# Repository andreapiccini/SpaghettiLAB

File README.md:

<p align="center">
  <a href="https://spaghetti-lab.my.canva.site/">Website</a> •
  <a href="https://spaghetti-lab.my.canva.site/join-newsletter">Newsletter</a>
</p>

# SpaghettiLAB Community

From prototype to product.

SpaghettiLAB Community is the open development platform for learning,
experimenting, and building modular embedded and IoT prototypes. It includes
reference hardware, firmware, local software, protocols, integrations, tests,
and examples without artificial feature restrictions.

A prototype is not automatically suitable for production. Professional
deployments also require qualified hardware, secure provisioning, verified
updates, release traceability, lifecycle maintenance, and accountable support.
Those production capabilities are developed and delivered separately so that
organizations can adopt SpaghettiLAB without weakening the open Community
platform.

## Repository structure

- `hardware/` — Core, Backbone, and Module reference designs.
- `firmware/` — Community firmware, SDKs, examples, and verification.
- `software/` — Local Studio, dashboard, Node-RED integration, and packages.
- `contracts/` — Public, language-neutral protocol contracts and golden fixtures.
- `examples/` — End-to-end example systems.
- `docs/` — Documentation licensing and notices.

The Community hardware tree intentionally contains editable KiCad sources, not
generated manufacturing packages. Official production files, factory tooling,
secure provisioning infrastructure, managed cloud services, and commercial
support are maintained separately.

## Hardware projects

- `hardware/core/core.kicad_pro`
- `hardware/backbone/backbone.kicad_pro`
- `hardware/modules/nfc-tag/nfc-tag.kicad_pro`

The KiCad source files embed the symbols and footprints already used by each
design. Some optional 3D models reference the `SPAGHETTI_LIB` environment
variable and are not required to open the schematic or PCB.

## Community and production

The Community platform is intended for education, research, development,
prototyping, and open products. Organizations may evaluate and extend it under
the applicable open-source and open-hardware licenses.

SpaghettiLAB Production adds the controlled engineering work needed to turn a
prototype into a supported product: qualified hardware, secure device identity,
signed releases, manufacturing support, managed updates, fleet operations, and
long-term maintenance.

## Citation

If you use SpaghettiLAB in research, publications, articles, videos, educational
material, or derivative projects, please cite:

> Piccini, A. (2026).  
> SpaghettiLAB: Modular Stackable Electronics Platform.  
> GitHub Repository.  
> https://github.com/andreapiccini/SpaghettiLAB

A machine-readable citation file is available in `CITATION.cff`.

## Licensing

The current Community generation retains the licenses already applied to its
components:

| Content | License |
|---|---|
| Firmware | GPL-3.0-or-later |
| Public applications and services | AGPL-3.0-or-later |
| Protocols and selected integration SDKs | Apache License 2.0 |
| Hardware reference designs | CERN-OHL-S-2.0 |
| Documentation | CC BY 4.0 |

See [`LICENSES.md`](LICENSES.md) for the exact repository map,
[`CONTRIBUTING.md`](CONTRIBUTING.md) for DCO contribution requirements, and
[`TRADEMARKS.md`](TRADEMARKS.md) for product identity rules. The copyleft transition
does not alter rights granted for earlier versions.

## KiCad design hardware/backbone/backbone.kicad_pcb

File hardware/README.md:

# Hardware sources

The Community repository tracks the editable KiCad projects required to study,
modify and build the public hardware: project, schematic, PCB, symbol, footprint
and related source assets.

Generated manufacturing outputs are intentionally not tracked. This includes
`production/` directories, Gerber and drill files, pick-and-place exports, BOMs,
netlists, fabrication ZIP archives and fabrication-toolkit local options. Generate
them from the reviewed KiCad sources when needed; official manufacturing releases
and production controls are maintained separately.

The ignore rules do not provide confidentiality for files already published in Git
history. They only prevent generated outputs from being added in future commits.

## KiCad library policy

Each public schematic embeds the symbols it uses and each public PCB embeds its
placed footprints, so the existing designs can be opened and edited without the
private Production repository. External 3D models are optional visualization assets:
missing models must not prevent schematic or PCB work.

Do not copy vendor 3D models or global workstation libraries into Community until
their origin and redistribution licence are recorded. New reusable public symbols or
footprints should be added as project-local, redistributable source assets rather
than relying on a developer's global KiCad configuration.

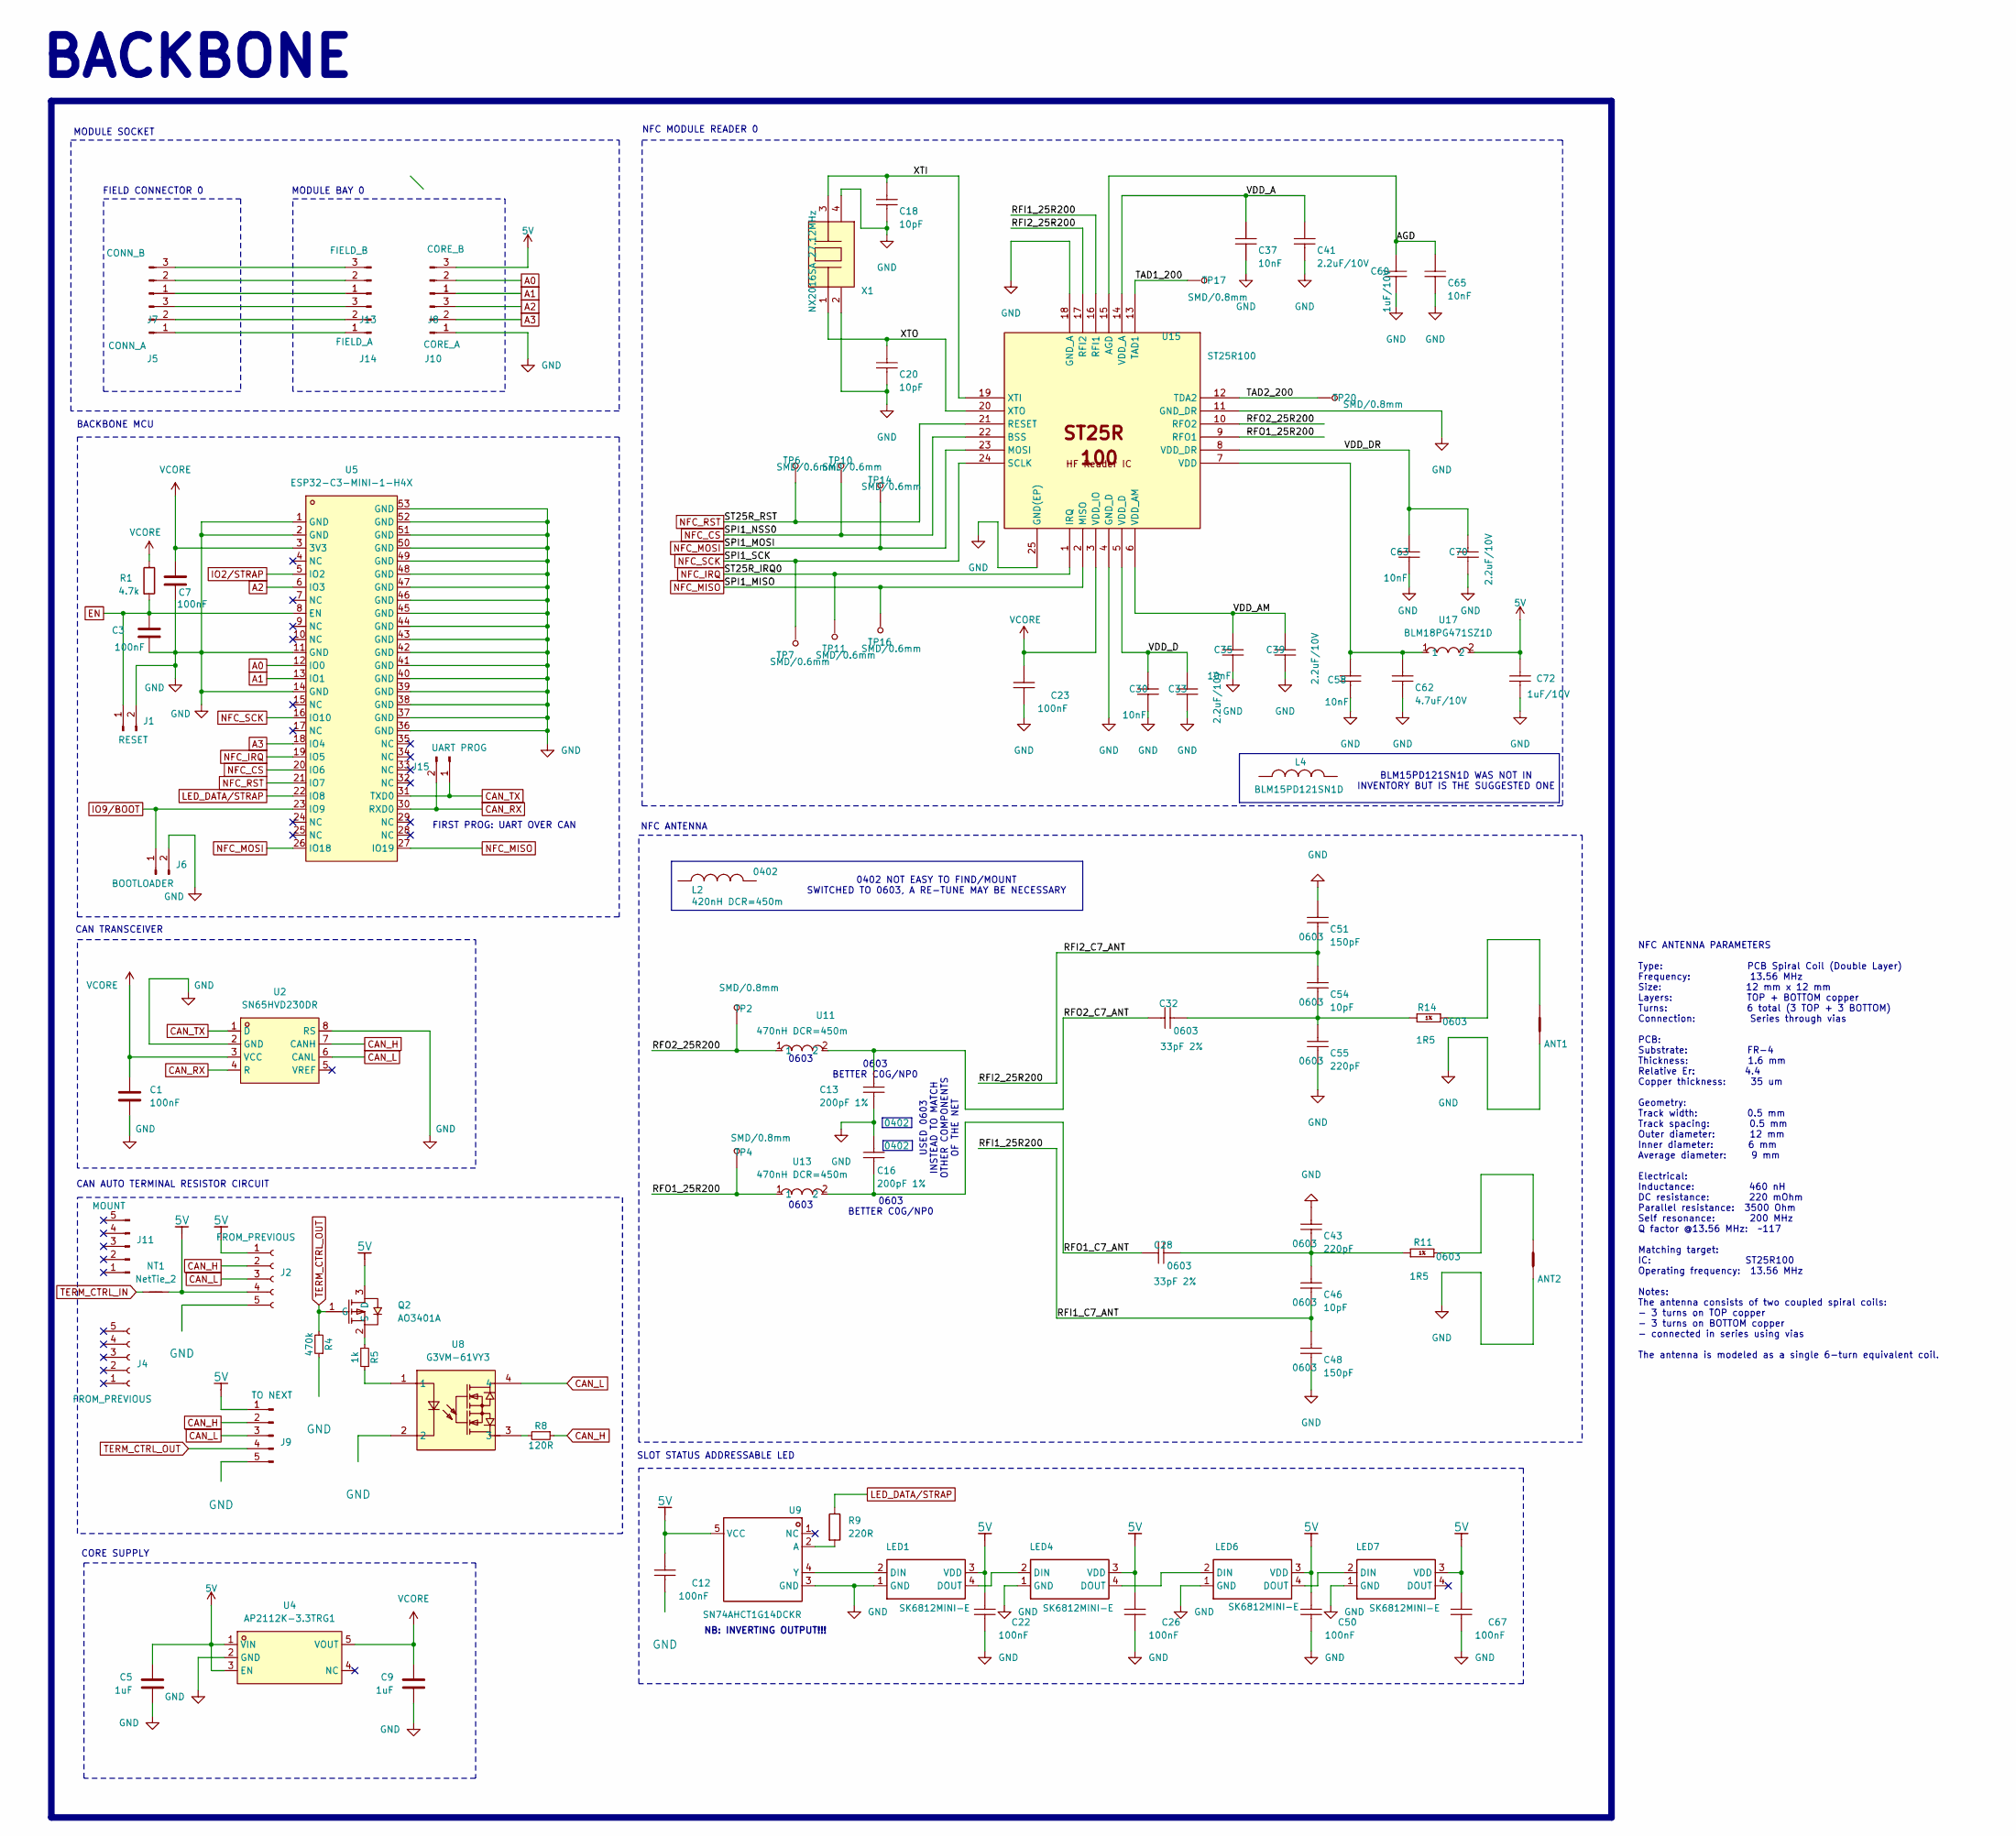
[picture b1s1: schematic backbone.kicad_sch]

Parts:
ANT1, ANT2: Net-Tie-Width-0.50mm; ST25Rxxx-ANT-12x12mm
C1: 100nF; C0603; MPN CL05B104KA5NNNC; LCSC Part Name C1591
C3, C7, C12, C22, C23, C26, C50, C67: 100nF; C0603; LCSC Part Name C1591
C5, C9: 1uF; C0603; LCSC Part Name C128624
C13, C16: 200pF 1%; C0603; MANUFACTURER PART NUMBER GRT1555C1H221FA02D; LCSC Part Name C1864235
C18, C20, C46, C54: 10pF; C0603; LCSC Part Name C1634
C28, C32: 33pF 2%; C0603; LCSC Part Name C3866175
C30, C35, C37, C58, C63, C65: 10nF; C0603; LCSC Part Name C100042
C33, C39, C41, C70: 2.2uF/10V; C0603; LCSC Part Name C23630
C43: 220pF; C0603; MANUFACTURER PART NUMBER GRM1885C1H241GA01J; LCSC Part Name C519500
C48, C51: 150pF; C0603; LCSC Part Name C2176758
C55: 220pF; C0603; LCSC Part Name C519500
C60, C72: 1uF/10V; C0603; LCSC Part Name C128624
C62: 4.7uF/10V; C0603; LCSC Part Name C326580
J1: RESET; PinHeader_1x02_P2.54mm_Vertical
J2, J4: FROM_PREVIOUS; PinSocket_1x05_P2.54mm_Horizontal
J5: CONN_A; PinSocket_1x03_P2.54mm_Vertical
J6: BOOTLOADER; PinHeader_1x02_P2.54mm_Vertical
J7: CONN_B; PinSocket_1x03_P2.54mm_Vertical
J8: CORE_B; PinSocket_1x03_P2.54mm_Vertical
J9: TO NEXT; PinHeader_1x05_P2.54mm_Horizontal
J10: CORE_A; PinSocket_1x03_P2.54mm_Vertical
J11: MOUNT; PinHeader_1x05_P2.54mm_Horizontal
J13: FIELD_B; PinSocket_1x03_P2.54mm_Vertical
J14: FIELD_A; PinSocket_1x03_P2.54mm_Vertical
J15: UART PROG; PinHeader_1x02_P2.54mm_Vertical
L2: 420nH DCR=450m; COILCRAFT-SELF-SERIE-0402DF
L4: BLM15PD121SN1D
LED1, LED4, LED6, LED7: SK6812MINI-E; LED-SMD_4P-L3.2-W2.8-LS5.9_SK6812MINI-E; Manufacturer Part SK6812MINI-E; LCSC Part Name C5149201
NT1: NetTie_2
Q2: AO3401A; SOT-23_L2.9-W1.3-P1.90-LS2.4-BR; MPN AO3401A; LCSC Part C15127
R1: 4.7k; R0603; LCSC Part Name C99782
R4: 470k; R0603; MPN RT0603FRE101KL; LCSC Part Name C114622
R5: 1k; R0603; MPN RT0603FRE101KL; LCSC Part Name C2907002
R8: 120R; R0603; MPN RT0603FRE101KL; LCSC Part Name C2906988
R9: 220R; R0603; LCSC Part Name C22962
R11, R14: 1R5; R0603; LCSC Part Name C2479753
TP2, TP4, TP17, TP20: SMD/0.8mm; TestPoint_Pad_D1.0mm
TP6, TP7, TP10, TP11, TP14, TP16: SMD/0.6mm; TestPoint_Pad_D1.0mm
U2: SN65HVD230DR; SOIC-8_L4.9-W3.9-P1.27-LS6.0-BL; MPN SN65HVD230DR; LCSC Part C12084
U4: AP2112K-3.3TRG1; SOT-25-5_L2.9-W1.6-P0.95-LS2.8-BL; MPN AP2112K-3.3TRG1; LCSC Part C51118
U5: ESP32-C3-MINI-1-H4X; WIFIM-SMD_ESP32-C3-MINI-1; MPN ESP32-C3-MINI-1-H4X; LCSC Part C41349510
U8: G3VM-61VY3; SMD-4_L4.6-W3.7-P2.54-LS7.0-TL; MPN G3VM-61VY3(TR); LCSC Part C2152318
U9: SN74AHCT1G14DCKR; SOT-353_L2.2-W1.4-P0.65-LS2.4-BR; Manufacturer Part SN74AHCT1G14DCKR; LCSC Part Name C7486
U11, U13: 470nH DCR=450m; IND-SMD_L1.6-W0.8-1; MPN LQW18CNR47J00D; LCSC Part C341701
U15: ST25R100; QFN-24_L4.0-W4.0-P0.50-TL-EP2.8; LCSC Part Name C29603415
U17: BLM18PG471SZ1D; L0603; MPN BLM18PG471SZ1D; LCSC Part C710387
X1: NX2016SA 27.12MHz; CRYSTAL-SMD_4P-L2.0-W1.6-BL; LCSC Part Name C3008209

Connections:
5V: C5.2, C12.2, C22.2, C26.2, C50.2, C67.2, C72.2, J2.1, J2.4, J8.3, J9.1, LED1.3 (VDD), LED4.3 (VDD), LED6.3 (VDD), LED7.3 (VDD), NT1.2, Q2.3 (D), U4.1 (VIN), U4.3 (EN), U9.5 (VCC), U17.2
/AGD: C60.2, C65.2, U15.15 (AGD)
/RFI1_25R200: C46.1, C48.2, U15.16 (RFI1)
/RFI2_25R200: C51.1, C54.2, U15.17 (RFI2)
/RFO1_25R200: TP4.1 (1_1), U13.1, U15.9 (RFO1)
/RFO1_C7_ANT: C16.1, C28.1, U13.2
/RFO2_25R200: TP2.1 (1_1), U11.1, U15.10 (RFO2)
/RFO2_C7_ANT: C13.2, C32.1, U11.2
/TAD1_200: TP17.1 (1_1), U15.13 (TAD1)
/TAD2_200: TP20.1 (1_1), U15.12 (TDA2)
/VDD_A: C37.2, C41.2, U15.14 (VDD_A)
/VDD_AM: C35.2, C39.2, U15.6 (VDD_AM)
/VDD_D: C30.2, C33.2, U15.5 (VDD_D)
/VDD_DR: C63.2, C70.2, U15.8 (VDD_DR)
/XTI: C18.2, U15.19 (XTI), X1.3
/XTO: C20.2, U15.20 (XTO), X1.1
A0: J8.2, U5.12 (IO0)
A1: J8.1, U5.13 (IO1); also elsewhere on the board
A2: J10.3, U5.6 (IO3); also elsewhere on the board
A3: J10.2, U5.18 (IO4); also elsewhere on the board
CAN_H: J2.2, J9.2, R8.1, U2.7 (CANH)
CAN_L: J2.3, J9.3, U2.6 (CANL), U8.4
CAN_RX: J15.2, U2.4 (R), U5.30 (RXD0)
CAN_TX: J15.1, U2.1 (D), U5.31 (TXD0)
EN: C3.1, J1.1, R1.2, U5.8 (EN)
GND: ANT1.1, ANT2.1, C1.2, C3.2, C5.1, C7.2, C9.1, C12.1, C13.1, C16.2, C18.1, C20.1, C22.1, C23.1, C26.1, C30.1, C33.1, C35.1, C37.1, C39.1, C41.1, C43.2, C48.1, C50.1, C51.2, C55.1, C58.1, C60.1, C62.1, C63.1, C65.1, C67.1, C70.1, C72.1, J1.2, J2.5, J6.2, J9.5, J10.1 (Pin_1_1), LED1.1 (GND), LED4.1 (GND), LED6.1 (GND), LED7.1 (GND), R4.1, U2.2 (GND), U2.8 (RS), U4.2 (GND), U5.1 (GND), U5.2 (GND), U5.11 (GND), U5.14 (GND), U5.36 (GND), U5.37 (GND), U5.38 (GND), U5.39 (GND), U5.40 (GND), U5.41 (GND), U5.42 (GND), U5.43 (GND), U5.44 (GND), U5.45 (GND), U5.46 (GND), U5.47 (GND), U5.48 (GND), U5.49 (GND), U5.50 (GND), U5.51 (GND), U5.52 (GND), U5.53 (GND), U8.2, U9.3 (GND), U15.4 (GND_D), U15.11 (GND_DR), U15.18 (GND_A), U15.25 (GND(EP)), X1.2, X1.4; also elsewhere on the board
IO2/STRAP: U5.5 (IO2)
IO9/BOOT: J6.1, U5.23 (IO9)
LED_DATA/STRAP: R9.1, U5.22 (IO8)
NFC_CS: TP10.1 (1_1), U5.20 (IO6), U15.22 (BSS)
NFC_IRQ: TP11.1 (1_1), U5.19 (IO5), U15.1 (IRQ)
NFC_MISO: TP16.1 (1_1), U5.27 (IO19), U15.2 (MISO)
NFC_MOSI: TP14.1 (1_1), U5.26 (IO18), U15.23 (MOSI)
NFC_RST: TP6.1 (1_1), U5.21 (IO7), U15.21 (RESET)
NFC_SCK: TP7.1 (1_1), U5.16 (IO10), U15.24 (SCLK)
unnamed: ANT1.2, R14.2
unnamed: ANT2.2, R11.2
unnamed: C28.2, C43.1, C46.2, R11.1
unnamed: C32.2, C54.1, C55.2, R14.1
unnamed 39: J7.1, J13.1; also elsewhere on the board
unnamed: J7.2, J13.2
unnamed: J7.3, J13.3
unnamed 42: J5.1, J14.1; also elsewhere on the board
unnamed: J5.2, J14.2
unnamed: J5.3, J14.3
unnamed: LED1.2 (DIN), U9.4 (Y)
unnamed: LED1.4 (DOUT), LED4.2 (DIN)
unnamed: LED4.4 (DOUT), LED6.2 (DIN)
unnamed: LED6.4 (DOUT), LED7.2 (DIN)
unnamed: Q2.2 (S), R5.2
unnamed: R5.1, U8.1
unnamed: R8.2, U8.3
unnamed: R9.2, U9.2 (A)
unnamed: C58.2, C62.2, U15.7 (VDD), U17.1
TERM_CTRL_OUT: J9.4, Q2.1 (G), R4.2
VCORE: C1.1, C7.1, C9.2, C23.2, R1.1, U2.3 (VCC), U4.5 (VOUT), U5.3 (3V3), U15.3 (VDD_IO)

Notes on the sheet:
SLOT STATUS ADDRESSABLE LED
MODULE SOCKET
FIELD CONNECTOR 0
FIRST PROG: UART OVER CAN
BLM15PD121SN1D WAS NOT IN INVENTORY BUT IS THE SUGGESTED ONE
0603 BETTER C0G/NP0
BACKBONE MCU
0402 NOT EASY TO FIND/MOUNT SWITCHED TO 0603, A RE-TUNE MAY BE NECESSARY
NFC ANTENNA
NB: INVERTING OUTPUT!!!
CAN TRANSCEIVER
MODULE BAY 0
USED 0603 INSTEAD TO MATCH OTHER COMPONENTS OF THE NET
0603
CAN AUTO TERMINAL RESISTOR CIRCUIT
BACKBONE
NFC ANTENNA PARAMETERS Type: PCB Spiral Coil (Double Layer) Frequency: 13.56 MHz Size: 12 mm x 12 mm Layers: TOP + BOTTOM copper Turns: 6 total (3 TOP + 3 BOTTOM) Connection: Series through vias PCB: Substrate: FR-4 Thickness: 1.6 mm Relative Er: 4.4 Copper thickness: 35 um Geometry: Track width: 0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
NFC MODULE READER 0
CORE SUPPLY

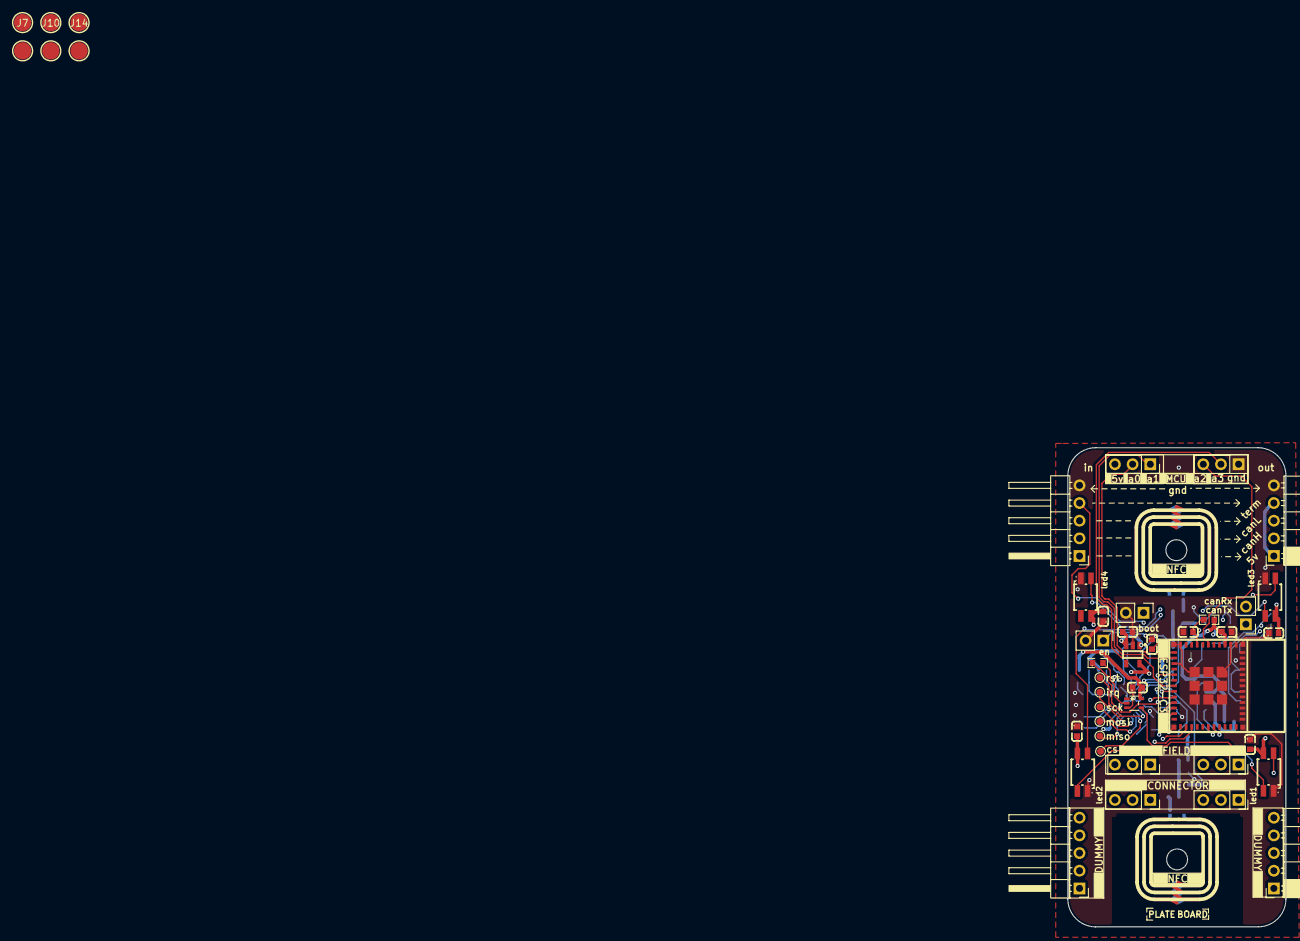
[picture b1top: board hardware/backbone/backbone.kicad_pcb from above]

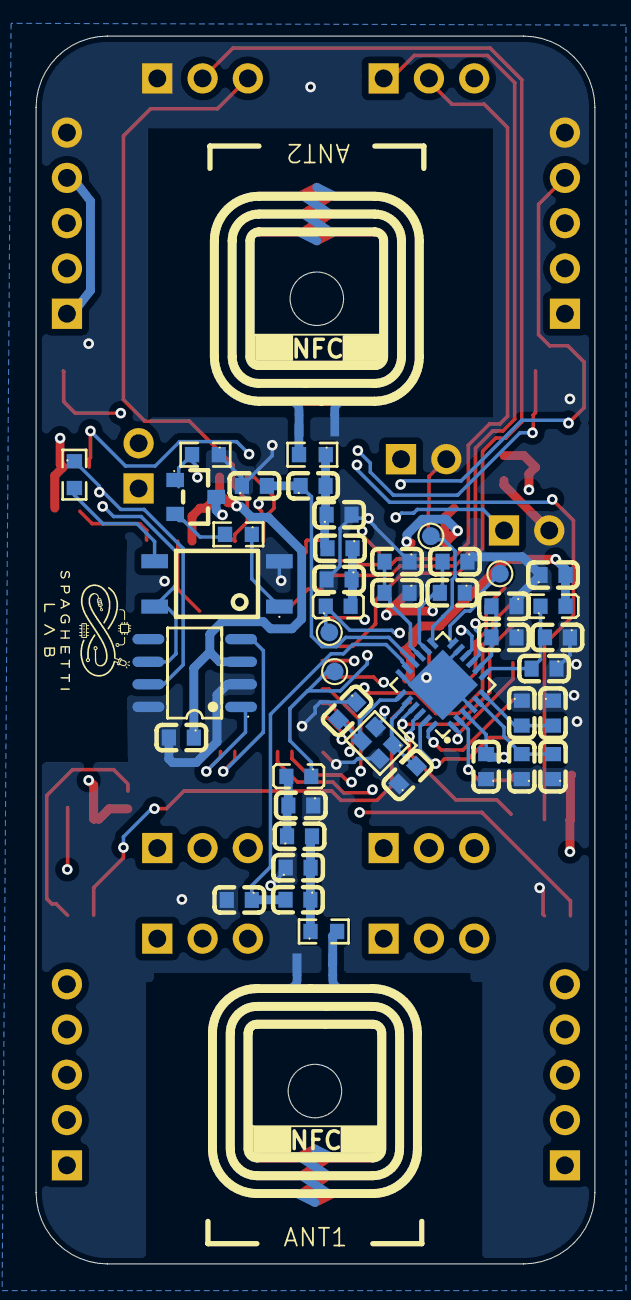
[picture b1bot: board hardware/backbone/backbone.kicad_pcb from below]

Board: 4 copper layers, 31.3 x 68.9 mm, 89 parts (46 on the bottom side), 55 nets.

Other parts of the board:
J5#2: CONN_A; SMD-1_BD2.0-H6.5
J7#2: CONN_B; SMD-1_BD2.0-H6.5
J8#2: CORE_B; SMD-1_BD2.0-H6.5
J10#2: CORE_A; PinSocket_1x03_P2.54mm_Vertical
J13#2: FIELD_B; SMD-1_BD2.0-H6.5
J14#2: FIELD_A; SMD-1_BD2.0-H6.5

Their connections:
A1: J8#2.1 (Pin_1_1); also elsewhere on the board
A2: J10#2.3; also elsewhere on the board
A3: J10#2.2; also elsewhere on the board
GND: J10#2.1; also elsewhere on the board
unnamed 39: J7#2.1 (Pin_1_1), J13#2.1 (Pin_1_1); also elsewhere on the board
unnamed 42: J5#2.1 (Pin_1_1), J14#2.1 (Pin_1_1); also elsewhere on the board

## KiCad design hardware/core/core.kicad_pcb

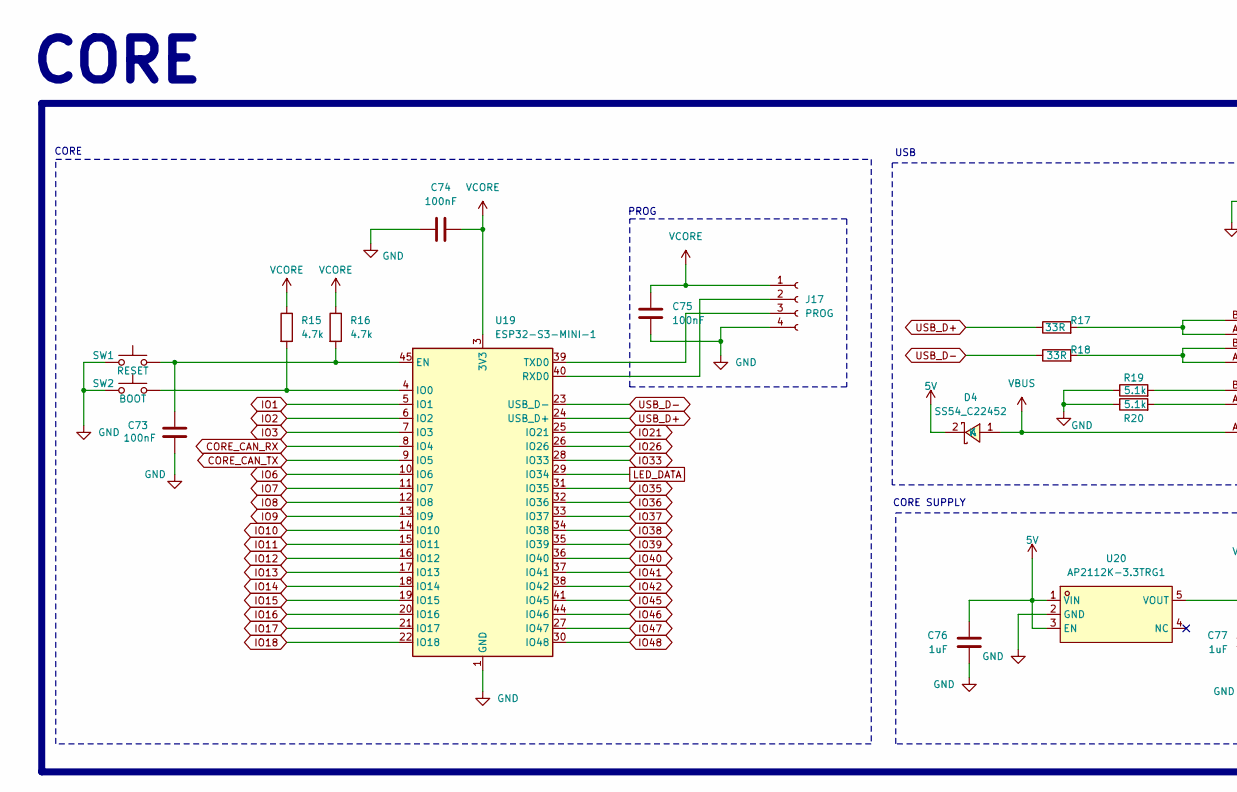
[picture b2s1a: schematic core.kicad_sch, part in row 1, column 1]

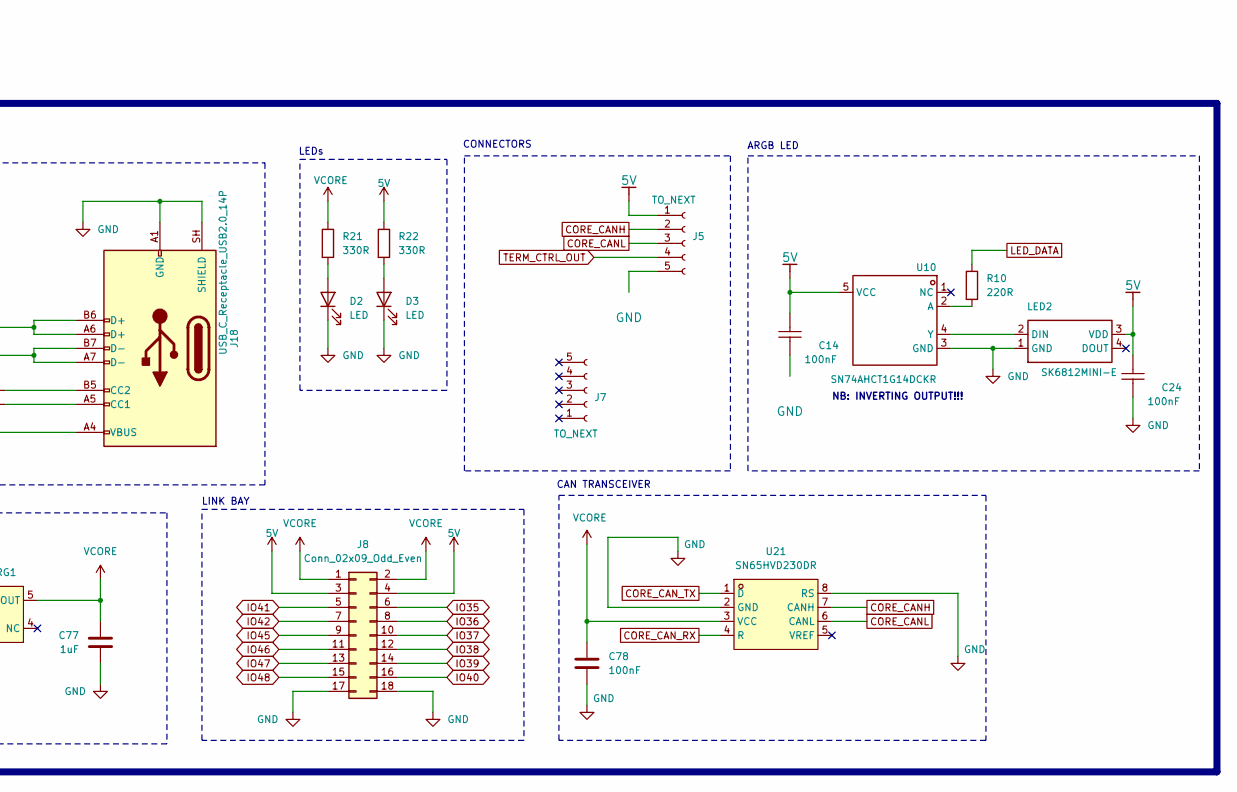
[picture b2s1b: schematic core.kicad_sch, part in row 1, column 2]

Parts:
C14, C24, C73, C74, C75: 100nF; C0603; LCSC Part C1591
C76, C77: 1uF; C0603; LCSC Part C128624
C78: 100nF; C0603; MPN CL05B104KA5NNNC; LCSC Part C1591
D2, D3: LED; LED0603-RD; LCSC Part C19273150
D4: SS54_C22452; SMA_L4.4-W2.8-LS5.4-R-RD; MPN SS54; LCSC Part C22452
J5, J7: TO_NEXT; PinSocket_1x05_P2.54mm_Horizontal
J8: Conn_02x09_Odd_Even; PinSocket_2x09_P2.54mm_Horizontal
J17: PROG; PinSocket_1x04_P2.54mm_Vertical
J18: USB_C_Receptacle_USB2.0_14P; USB-C-SMD_TYPEC-324G-BCP24; LCSC Part C920230
LED2: SK6812MINI-E; LED-SMD_4P-L3.2-W2.8-LS5.9_SK6812MINI-E; Manufacturer Part SK6812MINI-E; LCSC Part Name 工作电压5V、发光角度120°、灰度调节256级的RGB LED
R10: 220R; R0603; LCSC Part C22962
R15, R16: 4.7k; R0603; LCSC Part C99782
R17, R18: 33R; R0603; LCSC Part C2909394
R19, R20: 5.1k; R0603; LCSC Part C2907044
R21, R22: 330R; R0603; LCSC Part C105881
SW1: RESET; SW-SMD_4P-L5.1-W5.1-P3.70-LS6.5-TL_H1.5; LCSC Part C318884
SW2: BOOT; SW-SMD_4P-L5.1-W5.1-P3.70-LS6.5-TL_H1.5; LCSC Part C318884
U10: SN74AHCT1G14DCKR; SOT-353_L2.2-W1.4-P0.65-LS2.4-BR; Manufacturer Part SN74AHCT1G14DCKR; LCSC Part Name 单路施密特触发反相器
U19: ESP32-S3-MINI-1; ESP32-S2-MINI-1; LCSC Part C2913206
U20: AP2112K-3.3TRG1; SOT-25-5_L2.9-W1.6-P0.95-LS2.8-BL; MPN AP2112K-3.3TRG1; LCSC Part C51118
U21: SN65HVD230DR; SOIC-8_L4.9-W3.9-P1.27-LS6.0-BL; MPN SN65HVD230DR; LCSC Part C12084

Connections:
5V: C14.2, C24.2, C76.2, D4.2 (K), J5.1, J8.3, J8.4, LED2.3 (VDD), R22.1, U10.5 (VCC), U20.1 (VIN), U20.3 (EN)
CORE_CANH: J5.2, U21.7 (CANH)
CORE_CANL: J5.3, U21.6 (CANL)
CORE_CAN_RX: U19.8 (IO4), U21.4 (R)
CORE_CAN_TX: U19.9 (IO5), U21.1 (D)
GND: C14.1, C24.1, C73.2, C74.1, C75.1, C76.1, C77.1, C78.2, D2.1 (K), D3.1 (K), J5.5, J8.17, J8.18, J17.4, J18.A1 (GND), J18.A12 (GND), J18.B1 (GND), J18.B12 (GND), J18.SH (SHIELD), LED2.1 (GND), R19.1, R20.1, SW1.1, SW1.3, SW2.1, U10.3 (GND), U19.1 (GND), U19.2 (GND), U19.42 (GND), U19.43 (GND), U19.46 (GND), U19.47 (GND), U19.48 (GND), U19.49 (GND), U19.50 (GND), U19.51 (GND), U19.52 (GND), U19.53 (GND), U19.54 (GND), U19.55 (GND), U19.56 (GND), U19.57 (GND), U19.58 (GND), U19.59 (GND), U19.60 (GND), U19.61 (GND), U19.62 (GND), U19.63 (GND), U19.64 (GND), U19.65 (GND), U20.2 (GND), U21.2 (GND), U21.8 (RS)
IO1: U19.5 (IO1)
IO2: U19.6 (IO2)
IO3: U19.7 (IO3)
IO6: U19.10 (IO6)
IO7: U19.11 (IO7)
IO8: U19.12 (IO8)
IO9: U19.13 (IO9)
IO10: U19.14 (IO10)
IO11: U19.15 (IO11)
IO12: U19.16 (IO12)
IO13: U19.17 (IO13)
IO14: U19.18 (IO14)
IO15: U19.19 (IO15)
IO16: U19.20 (IO16)
IO17: U19.21 (IO17)
IO18: U19.22 (IO18)
IO21: U19.25 (IO21)
IO26: U19.26 (IO26)
IO33: U19.28 (IO33)
IO35: J8.6, U19.31 (IO35)
IO36: J8.8, U19.32 (IO36)
IO37: J8.10, U19.33 (IO37)
IO38: J8.12, U19.34 (IO38)
IO39: J8.14, U19.35 (IO39)
IO40: J8.16, U19.36 (IO40)
IO41: J8.5, U19.37 (IO41)
IO42: J8.7, U19.38 (IO42)
IO45: J8.9, U19.41 (IO45)
IO46: J8.11, U19.44 (IO46)
IO47: J8.13, U19.27 (IO47)
IO48: J8.15, U19.30 (IO48)
LED_DATA: R10.1, U19.29 (IO34)
unnamed: D2.2 (A), R21.2
unnamed: D3.2 (A), R22.2
unnamed: J17.2, U19.40 (RXD0)
unnamed: J17.3, U19.39 (TXD0)
unnamed: J18.A5 (CC1), R20.2
unnamed: J18.B5 (CC2), R19.2
unnamed: J18.A6 (D+), J18.B6 (D+), R17.2
unnamed: J18.A7 (D-), J18.B7 (D-), R18.2
unnamed: LED2.2 (DIN), U10.4 (Y)
unnamed: R10.2, U10.2 (A)
unnamed: C73.1, R16.2, SW1.2, U19.45 (EN)
unnamed: R15.2, SW2.2, U19.4 (IO0)
TERM_CTRL_OUT: J5.4
USB_D+: R17.1, U19.24 (USB_D+)
USB_D-: R18.1, U19.23 (USB_D-)
VBUS: D4.1 (A), J18.A4 (VBUS), J18.A9 (VBUS), J18.B4 (VBUS), J18.B9 (VBUS)
VCORE: C74.2, C75.2, C77.2, C78.1, J8.1, J8.2, J17.1, R15.1, R16.1, R21.1, U19.3 (3V3), U20.5 (VOUT), U21.3 (VCC)

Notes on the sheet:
CAN TRANSCEIVER
CORE SUPPLY
CORE
LINK BAY
USB
LEDs
NB: INVERTING OUTPUT!!!
PROG
CONNECTORS
ARGB LED

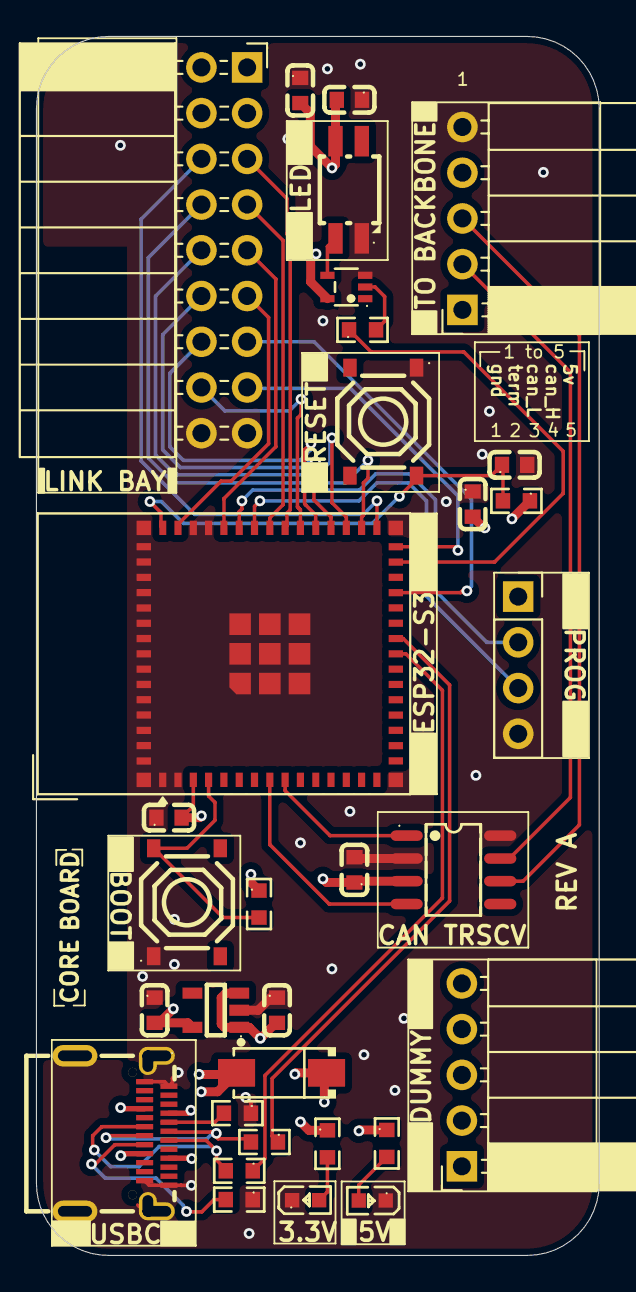
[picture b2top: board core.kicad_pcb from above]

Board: 4 copper layers, 31.3 x 67.7 mm, 32 parts (0 on the bottom side), 35 nets.

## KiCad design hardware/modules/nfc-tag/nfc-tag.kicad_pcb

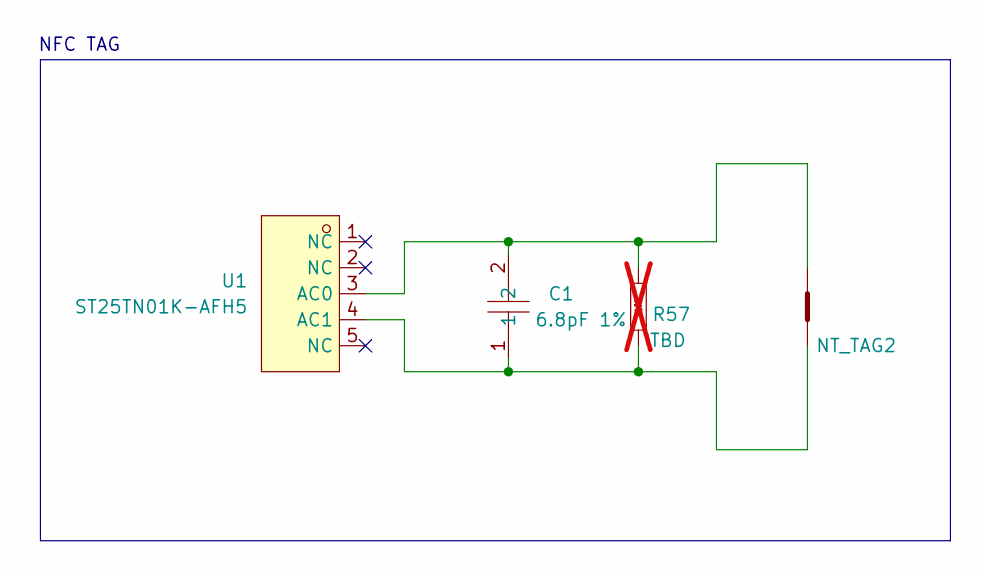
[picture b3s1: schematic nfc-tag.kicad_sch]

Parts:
C1: 6.8pF 1%; C0402; MPN GCM1555C1H6R8FA16D; LCSC Part C1864373
NT_TAG2: Net-Tie-Width-0.10mm; NetTie-3_SMD_Pad0.5mm
R57: TBD; R0402; not fitted
U1: ST25TN01K-AFH5; UFDFPN-5_L1.7-W1.4-P0.40-BL; MPN ST25TN01K-AFH5; LCSC Part C3303589

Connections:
unnamed: C1.2, NT_TAG2.2, R57.2, U1.3 (AC0)
unnamed: C1.1, NT_TAG2.1, R57.1, U1.4 (AC1)

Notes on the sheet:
NFC TAG

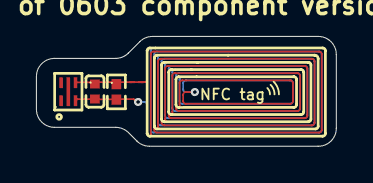
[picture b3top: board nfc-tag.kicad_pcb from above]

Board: 2 copper layers, 16.7 x 6.1 mm, 4 parts (0 on the bottom side), 2 nets.
